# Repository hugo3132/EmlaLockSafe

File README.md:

# All documentation can be found under https://hugo3132.github.io/EmlaLockSafe/index.html

# EmlaLockSafe
This project is about controlling a cheap digital safe from a local hardware store using the API of emlalock https://www.emlalock.com.

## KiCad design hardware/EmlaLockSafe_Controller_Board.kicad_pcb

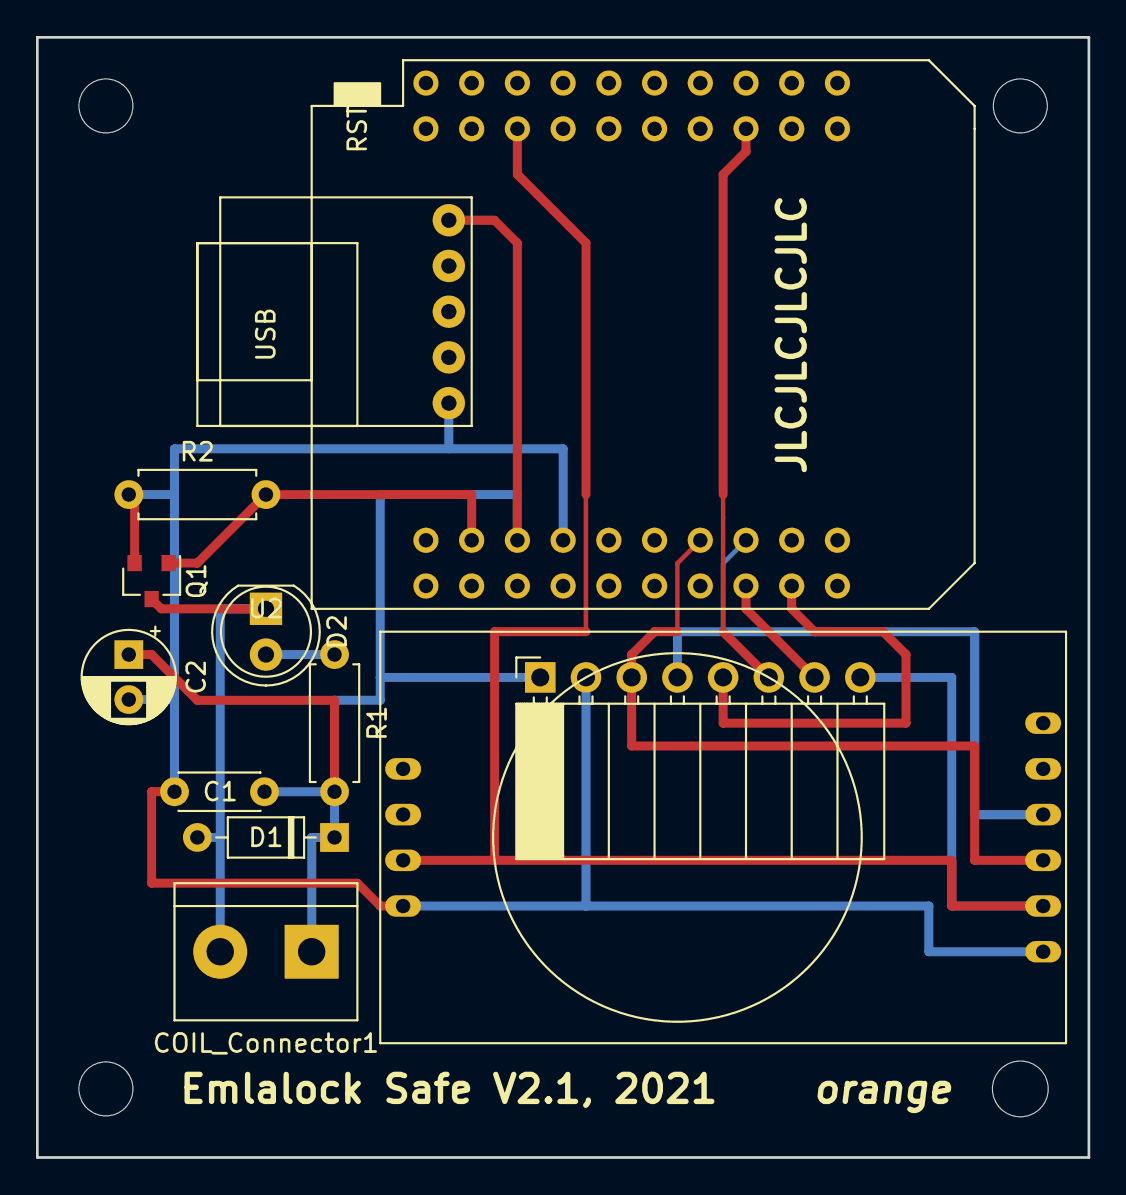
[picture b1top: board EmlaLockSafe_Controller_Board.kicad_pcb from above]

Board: 2 copper layers, 58.4 x 62.2 mm, 12 parts (0 on the bottom side), 11 nets.

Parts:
C1: 100n; C_Disc_D4.3mm_W1.9mm_P5.00mm
C2: 100µ; CP_Radial_D5.0mm_P2.50mm
COIL_Connector1: Screw_Terminal_01x02; TerminalBlock_bornier-2_P5.08mm
D1: 1N4148; D_DO-35_SOD27_P7.62mm_Horizontal
D2: LED; LED_D5.0mm
LCD/Encoder_Connecor1: Conn_01x08; PinSocket_1x08_P2.54mm_Horizontal
Q1: IRLML6244; SOT-23
R1: 470; R_Axial_DIN0207_L6.3mm_D2.5mm_P7.62mm_Horizontal
R2: 1k; R_Axial_DIN0207_L6.3mm_D2.5mm_P7.62mm_Horizontal
RTC1: DS3231_Module_AzDelivery
U1: mini_esp32; ESP32_mini
U2: MicroUSBBreakout

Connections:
+3V3: LCD/Encoder_Connecor1.8, RTC1.5, U1.16
+5V: C1.1, C2.1, COIL_Connector1.1, D1.1, LCD/Encoder_Connecor1.1, R1.2, U1.35, U2.1
COIL: Q1.1, R2.2, U1.37
ENC_CLK: LCD/Encoder_Connecor1.5, U1.24
ENC_DT: LCD/Encoder_Connecor1.6, U1.6
ENC_SW: LCD/Encoder_Connecor1.7, U1.26
GND: C1.2, C2.2, LCD/Encoder_Connecor1.2, Q1.2, R2.1, RTC1.6, U1.33, U2.5
unnamed: COIL_Connector1.2, D1.2, D2.1, Q1.3
unnamed: D2.2, R1.1
SCL: LCD/Encoder_Connecor1.4, RTC1.3, U1.25
SDA: LCD/Encoder_Connecor1.3, RTC1.4, U1.27

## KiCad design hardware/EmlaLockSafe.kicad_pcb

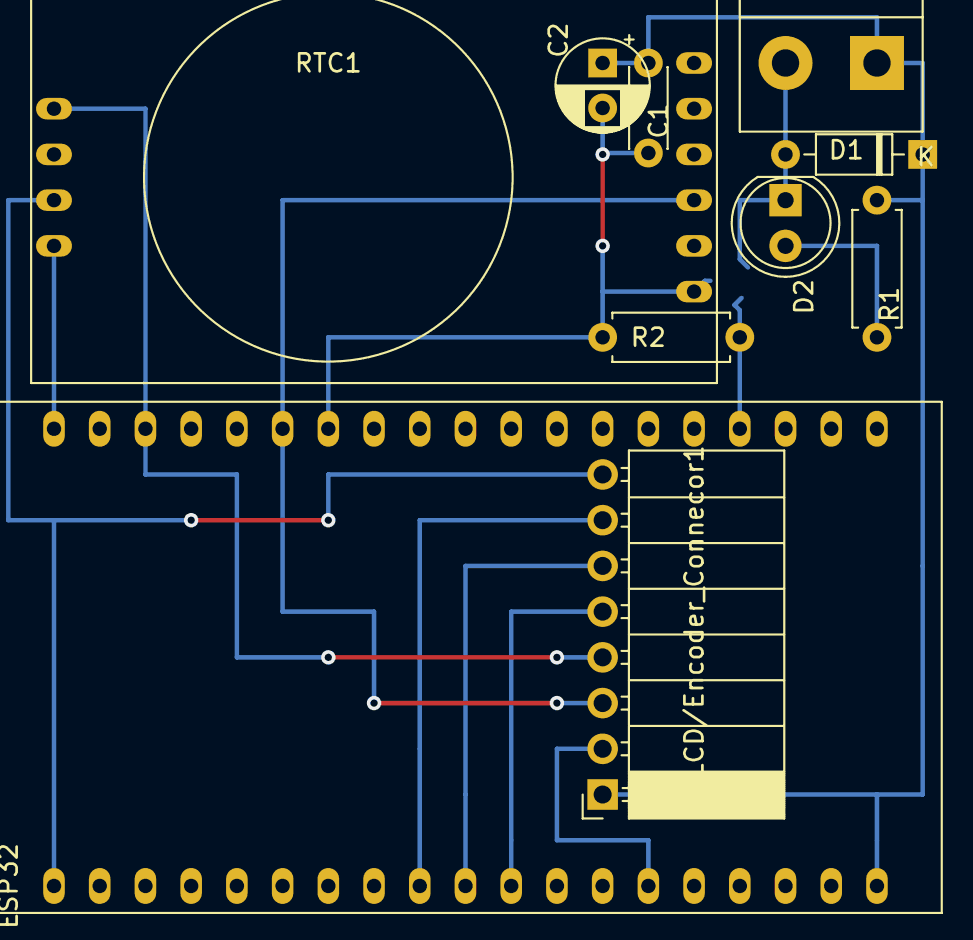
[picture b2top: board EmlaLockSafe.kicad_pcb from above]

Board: 4 copper layers, 11 parts (1 on the bottom side), 11 nets.

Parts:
C1: 100n; C_Disc_D4.3mm_W1.9mm_P5.00mm
C2: 100µ; CP_Radial_D5.0mm_P2.50mm
COIL_Connector1: Screw_Terminal_01x02; TerminalBlock_bornier-2_P5.08mm
D1: 1N4148; D_DO-35_SOD27_P7.62mm_Horizontal
D2: LED; LED_D5.0mm
ESP32: ESP32_NodeMCU_Module_AzDelivery
LCD/Encoder_Connecor1: Conn_01x08; PinSocket_1x08_P2.54mm_Horizontal
Q1: IRLML6244; SOT-23
R1: 470; R_Axial_DIN0207_L6.3mm_D2.5mm_P7.62mm_Horizontal
R2: 1k; R_Axial_DIN0207_L6.3mm_D2.5mm_P7.62mm_Horizontal
RTC1: DS3231_Module_AzDelivery

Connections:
+3V3: ESP32.1, LCD/Encoder_Connecor1.8, RTC1.5
+5V: C1.1, C2.1, COIL_Connector1.1, D1.1, ESP32.19, LCD/Encoder_Connecor1.1, R1.2
COIL: ESP32.23, Q1.1, R2.2
ENC_CLK: ESP32.11, LCD/Encoder_Connecor1.5
ENC_DT: ESP32.10, LCD/Encoder_Connecor1.6
ENC_SW: ESP32.9, LCD/Encoder_Connecor1.7
GND: C1.2, C2.2, ESP32.GND, LCD/Encoder_Connecor1.2, Q1.2, R2.1, RTC1.6
unnamed: COIL_Connector1.2, D1.2, D2.1, Q1.3
unnamed: D2.2, R1.1
SCL: ESP32.36, LCD/Encoder_Connecor1.4, RTC1.3
SDA: ESP32.33, LCD/Encoder_Connecor1.3, RTC1.4

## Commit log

2020-08-15 added basic folder structure
2020-08-15 Added Hardware-List
2020-08-15 Added Blink Example to test board
2020-08-15 First version
2020-08-16 - Added lock state - Updated manual locking
2020-08-16 Updated Locked view Added Temperature to vview
2020-08-16 -Added interface to Emlalock API -Added names to all views
2020-08-17 Update Current Hardwarelist.txt
    Added Safe
2020-08-17 Finished implementation of emergency key
2020-08-19 Added schematic
2020-08-19 - Added 2 Defines describing the COIL State of the digital pin - Renamed defines of the encoder to the actual pin names - reordered the initialization of the modules to be able to enter the emergency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
2020-08-29 Added missing library
2020-08-30 Fixed unlock key menu which did not display a freshly generated key
2020-08-31 added image from coil
2020-08-31 resized picture
2020-08-31 Updated schematics
2020-08-31 added svg versions of schematic
2020-08-31 Added some pictures
2020-08-31 added picture of unlock key
2020-08-31 Update README.md
    TBD...
2020-09-01 Added compressed STL file of case
2020-09-01 Updated section d escribing hardware
2020-09-05 added image of safe
2020-09-05 added support for hygiene openings
2020-09-05 updated picture
2020-09-05 force refresh part 1
2020-09-05 force refresh part 2
2020-09-05 force refresh maybe now?
2020-09-05 Added Activity Diagram
2020-09-05 updated example views
2020-09-09 added missing parameter documentation
2020-09-26 Updated Hygiene Opening
2020-09-27 - added new variable mode - added base type for enums
2020-09-27 - added offline mode which disables the API - disabled API request if a manual timer is used
2020-09-27 Set mode if a manual timer is used
2020-09-27 fixed use of manual timer even without wifi
2020-09-27 updated activity diagram
2021-02-20 In case an session is aborted on emlalock the safe uses the last enddate and switches to manual mode until then.
2021-08-26 quick and dirty hack to get the api working again
2021-08-28 improved api reader
2021-12-08 Updated List of Libraries
2021-12-08 Added Library for ESP32 Mini
2021-12-11 Moved SubModule
2021-12-11 Updated to V2
2021-12-11 Updated Hardwarelist
2021-12-12 - Moved attaching and detaching interrupts to separate class - Added option to execute code without interrupts using lambdas
2021-12-12 - started moving configuration to a configuration::Configuration - added webserver to configure wifi settings
2021-12-12 Added Configuration Webserver for Non-Wifi Settings
2021-12-17 Switched to Captive Portal for the configuration of the WiFi settings
2021-12-17 moved pin configuration
2021-12-17 fixed some copy past errors
2021-12-17 Marked old harware layout in pictures
2021-12-17 added 3D rendering of pcb
2021-12-17 Added pictures of configuration process
2021-12-17 - resized picture - added picture what is shown in software configuration mode
2021-12-17 Started adding howto
2021-12-17 Added Display Backlight Timeout as configurable parameter
2021-12-17 Added configuration flag to automatically lock the safe after the time of an hygiene opening is over
2021-12-19 - added back entry - fixed wrong comparison for IP check
2021-12-19 enabled debug logging
2021-12-19 apply configuration changes without reboot
2021-12-19 added reboot entry
2021-12-19 Added DoxyGen
2021-12-19 Set theme jekyll-theme-slate
2021-12-19 Try to add an action to automatically generate doxygen
2021-12-19 deploy: 302c8b87852e34c14cfc9a842d22d0e03fcb4b28
2021-12-19 Update Doxyfile
2021-12-19 moved doxyfile
2021-12-19 deploy: aa719801e13b99100db881c7441e83fc9e341ce4
2021-12-19 updated documentation
2021-12-19 deploy: 5aa90eb3833df856e4ec239b2ba66d037f7dc77c
2021-12-20 Updated Controller Board
2021-12-20 removed rendered PCB
2021-12-20 added a workspace file
2021-12-20 removed unnecessary call of HardwareTestView
2021-12-20 Added try catch to attach the interrupts again in case of an exception
2021-12-20 added menu entry to change the wifi settings
2021-12-20 moved zones.json to ConfigurationServer
2021-12-20 updated formatting
2021-12-20 split code into several functions
2021-12-20 moved a few labels
2021-12-20 deploy: 2c3f68834a14165f2884fb287092a0e2eca643a8
2021-12-20 added reference back to github
2021-12-20 deploy: 565e3a4a284603f115810473d25156de77593304
2021-12-20 Add a reference to the html file used for the configuration
2021-12-20 updated view
2021-12-20 deploy: 77592e3c74e9a491471e4f16e5a7a62346dc694a
2021-12-20 Added Documentation of Main configuration server
2021-12-20 deploy: 104e0102907f913db87495da73100f654bff7d14
2021-12-20 updated docu
2021-12-20 deploy: b0478ed23accbbf1bc65b0746eaaef61f783cbe1
2021-12-22 moved documentation from readme.md to doxygen
2021-12-22 Moved documentation to doxygen
2021-12-22 deploy: 0ea5281601abd486c3014a4ce7871526bea8ddcf
2021-12-23 Added all menus to the documentation
2021-12-23 deploy: 088bb1402ff65a4ae426807e49aa032ba7e32f40
2021-12-23 removed format flash which would break the webservers
2021-12-23 removed no longer required pictures
2021-12-23 added a note
2021-12-23 deploy: e2458add5369e0682ee23e4ead650f62d2c833e4
2021-12-23 finalized user manual part of documentation
2021-12-23 deploy: 2ebdc142eeae5072f30ff0717c89ee57555c24d7
2021-12-24 Moved documentation
2021-12-24 deploy: 0083790f5fbbfac7ba81e2959277ef501affb3db
2021-12-24 deploy: 3b2c45ab92c5522079f491d11743d3ddba55c8c8
2021-12-27 removed debug code
2021-12-27 Update Current Hardwarelist.txt
    Added link to origninal controller board which is available again
2021-12-27 deploy: 0af82d18ebf7f7d19ef2ca3be072bc5f92282908
2021-12-27 deploy: 49e4e623ece69c5f25c7dba0a7fcd45db06805ef
2021-12-27 updated hardware documentation
2021-12-27 deploy: 6f7d7318d919c13ac1b008c4cde49d573ec25a22
2021-12-28 Added configuration page to doxygen as preview
2021-12-28 deploy: 642d6c88fc8198f12e65a456bbee8228d73c9cf6
2021-12-28 Added the option to limit the time span when the safe can be opened
2021-12-28 deploy: 07dba1bcde64d031c945080ced65ae1d002218da
2021-12-28 added default value for
2021-12-28 deploy: 9fcc890b7a30de3cc5808dad5b4bd9c3bd9d4368
2021-12-29 Moved Emergency Key to configuration and made it visible in the configuaration server
2021-12-29 added mentioning of emergency key in config server
2021-12-29 deploy: 2a4e3eb1d75f13f014bf84d4b95ed71537144688
2021-12-30 mark documentation folder as documentation to have no longer and impact on the repository language
2021-12-30 deploy: 0c3f61904169f88f0c3a054f19681e34f4960ae2
2021-12-30 mark documentation folder as documentation to have no longer and impct on the repository language
2021-12-30 deploy: ae9dacdf58826e7dfd780bcffd69761b0cdb6a4f
2021-12-30 deploy: 4eb544d4025af583c1a951124f1808c5569d29b5
2021-12-30 deploy: 0b98329120cfa39830dcc6bca7d69870ccfcb198
2021-12-30 Added an option to reset the configuration
2021-12-30 deploy: 556fe053b1354b7c4de41f8eec4e5cae4be131c4
2021-12-31 Updated pictures
2021-12-31 deploy: cb3466be362c1090cee823b6f61c52dc79035b9b
2022-01-03 Added option to remote control the safe using the browser
2022-01-03 deploy: ca78a1ba00bef4edcd8260dd1ac497d0e4e5bde3
2022-01-03 added comment to the source of the file
2022-01-03 deploy: cd55f03bbabbe4b382929e86b88aa4eadcf500b9
2022-01-03 added option to reflect backlight state of LCD in remote control mode
2022-01-03 deploy: 286f01111b57c621304760b4e7f088cb171fbdf3
2022-01-03 added missing files to documentation output
2022-01-03 deploy: b4fb5f1875d6ec303bb075cc22eff561cbeccb81
2022-01-04 fixed dns lookup, updated documentation to reflect that the safe can be reached by name
2022-01-04 deploy: b9aa796d1af5fed9bddc24003169f67ae84493e4
2022-01-06 - Changed mounting holes to 3mm - Changed 5V & 3,3V wiring to allow to use the PCB without the RTC module
2022-01-06 deploy: 597c60131b2053a20837187dbd4ee251fa681753
2022-01-06 made behavior configurable if a session is ended as failed session
2022-01-06 deploy: b49de48f0b74718b13c58b4edd70c45e8b9fee69
2022-03-18 Added Optional Switch which can be soldered to the ESP to enable the configuration server when the safe is open
2022-03-18 deploy: c6688bda8c7b901984b7012cddf97b12bb7b3b0d
2022-04-08 added stl of LCD housing
2022-04-08 deploy: 1e25a237305167ffd93f9a7e403d17ae12cb1e2e
2022-04-08 updated link to STL file
2022-04-08 deploy: cbd6a3f4580983847cb7ab4df420e028c62bc7b5
2022-04-09 added mounting brackets created by naaitsab
2022-04-09 deploy: 83b802f1ec1e9253dacd92917a0c50bdc8da0676
2022-04-09 reorganized 3d printed parts, added stl files for adapter plate and pcb holder
2022-04-09 deploy: e43f5f70279529bde5ce7b0b0e1e6aa7f47da82b
2022-04-09 updated hardware list
2022-04-09 deploy: 6b4f964f0bbdb9ec20d934b661aada04f6a22f90
2022-04-09 deploy: 48922efcf7eececd558946c084a28cdc4eb2680c
2022-04-15 added pictures of modifications
2022-04-15 deploy: 60c80dce89c1b360d97c4a9d63abe0dc6bb976cf
2022-04-15 added pictures of naaitsab's modifications
2022-04-15 deploy: 4f8c6562ebb15c6fba0b7f528122420f23791561
2022-04-15 deploy: 0bc864e27d92ca9935170dc7cd8c77d72c8303e7
2022-05-24 Added a new version of the housing
2022-05-24 deploy: cfbac19114190a248285cbe17175c308325a10de
2022-05-24 deploy: cb270625a420590d4d4ca8246925aeab50745cf4
2022-05-24 reverted accidentally removed file
2022-05-24 deploy: 58d51dfd8ee1156e0812205e87aeaa1801aa4bb4
2022-05-24 deploy: 5436288dc4840152e1ae6f584659b8702d7cb251
